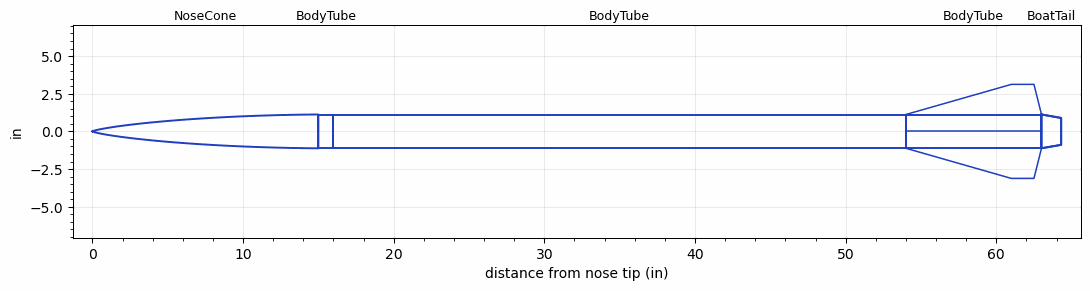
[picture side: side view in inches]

<RASAeroDocument>
 <FileVersion>2</FileVersion>
 <RocketDesign>
  <NoseCone>
   <Length>15</Length>
   <Diameter>2.242</Diameter>
   <Shape>LV-Haack</Shape>
   <Location>0</Location>
  </NoseCone>
  <BodyTube>
   <Length>1</Length>
   <Diameter>2.242</Diameter>
   <Location>15</Location>
  </BodyTube>
  <BodyTube>
   <Length>38</Length>
   <Diameter>2.242</Diameter>
   <Location>16</Location>
  </BodyTube>
  <BodyTube>
   <Length>9</Length>
   <Diameter>2.242</Diameter>
   <Location>54</Location>
   <BoattailLength>1.305</BoattailLength>
   <BoattailRearDiameter>1.785</BoattailRearDiameter>
   <Fin>
    <Count>4</Count>
    <Chord>9</Chord>
    <Span>2</Span>
    <SweepDistance>7</SweepDistance>
    <TipChord>1.5</TipChord>
    <Thickness>0.1</Thickness>
    <LERadius>0.02</LERadius>
    <Location>9</Location>
    <AirfoilSection>Hexagonal</AirfoilSection>
    <FX1>0.4</FX1>
    <FX3>0.4</FX3>
   </Fin>
  </BodyTube>
  <BoatTail>
   <Length>1.305</Length>
   <Diameter>2.242</Diameter>
   <RearDiameter>1.785</RearDiameter>
   <Location>63</Location>
  </BoatTail>
  <Surface>Camouflage Paint</Surface>
  <ModifiedBarrowman>True</ModifiedBarrowman>
  <Turbulence>True</Turbulence>
  <UseBooster1>False</UseBooster1>
  <UseBooster2>False</UseBooster2>
 </RocketDesign>
 <LaunchSite>
  <Altitude>2000</Altitude>
  <Pressure>0</Pressure>
  <RodAngle>2</RodAngle>
  <RodLength>8</RodLength>
  <Temperature>85</Temperature>
  <WindSpeed>10</WindSpeed>
 </LaunchSite>
 <Recovery>
  <Altitude1>1000</Altitude1>
  <Altitude2>1000</Altitude2>
  <DeviceType1>None</DeviceType1>
  <DeviceType2>None</DeviceType2>
  <Event1>False</Event1>
  <Event2>False</Event2>
  <Size1>1</Size1>
  <Size2>1</Size2>
  <EventType1>None</EventType1>
  <EventType2>None</EventType2>
  <CD1>1.33</CD1>
  <CD2>1.33</CD2>
 </Recovery>
 <SimulationList>
  <Simulation>
   <SustainerEngine>M1378LR  (Loki)</SustainerEngine>
   <SustainerLaunchWt>12.7</SustainerLaunchWt>
   <SustainerNozzleDiameter>1.5</SustainerNozzleDiameter>
   <SustainerCG>38.24</SustainerCG>
   <SustainerIgnitionDelay>0</SustainerIgnitionDelay>
   <Booster1SeparationDelay>0</Booster1SeparationDelay>
   <Booster1IgnitionDelay>0</Booster1IgnitionDelay>
   <IncludeBooster1>False</IncludeBooster1>
   <Booster2Delay>0</Booster2Delay>
   <IncludeBooster2>False</IncludeBooster2>
   <TimetoApogee>45.86831</TimetoApogee>
   <MaxAltitude>47660.44</MaxAltitude>
   <MaxVelocity>3272.888</MaxVelocity>
   <OptimumWt>11.03312</OptimumWt>
   <OptimumMaxAlt>11.03312</OptimumMaxAlt>
  </Simulation>
 </SimulationList>
</RASAeroDocument>
